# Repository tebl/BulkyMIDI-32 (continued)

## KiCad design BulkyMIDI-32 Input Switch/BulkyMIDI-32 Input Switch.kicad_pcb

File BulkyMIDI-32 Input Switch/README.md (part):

# BulkyMIDI-32 Input Switch
The complete *BulkyMIDI-32* consists of several separate PCB designs, many of them adding entirely separate functionality that can be used with or even without the main unit. This specific module, once fully assembled will allow you to switch between four different MIDI-inputs.

The selected input will be hooked up to the three thru-ports on the unit, allowing you to quickly switch between different keyboards, vintage computers and so on. Think of it as a simple 4-to-1 *MIDI Input Selector* chained to a 1-to-3 *MIDI Thru Box*. If you came here looking for something to switch between different audio sources, then have a look at [BulkyMIDI-32 Audio Switch](https://github.com/tebl/BulkyMIDI-32/tree/main/BulkyMIDI-32%20Audio%20Switch) instead.

For the design itself, I didn't want to use a microcontroller for such a trivial task, so it is implemented using logic chips instead. The end result is a set of flip-flops with a master reset, this latches the button pushed and you get an exciting little click from the corresponding relay. While this does mean that the device only switches electrical signals with the caveat that it doesn't have an understanding of MIDI-messages, and so it will cut regardless of what's passing through it. The upside is that since there is not processing, there is no *significant* delay added to it either.

- [1> Building the device](#1-building-the-device)
  - [1.1> Soldering it together](#11-soldering-it-together)
  - [1.2> Without front panel](#12-without-front-panel)
  - [1.3> Including front panel](#13-including-front-panel)
  - [1.4> Finishing touches](#14-finishing-touches)
- [2> Schematic](#2-schematic)
- [3> BOM](#3-bom)

# 1> Building the device
Building a device such as this assumes you have at least minor experience soldering things together, recommended is that you at the very least have access to a soldering station with adjustable temperature. If currently available, you should probably start with 60/40 rosin core solder as the lead-free alternatives tends to be a bit harder to work with.

With requirements for basic equipment sorted, we need to talk a bit about what you want to achieve while building this project. The reason I ask is that while you can build a functional *BulkyMIDI-32 Input Switch* by using this module by itself, there is certainly a case for having the option of building a complete version of it - this would normally include a front panel, a faceplates for the top of the unit as well as a cosmetic one to go on the front. 

Now that you know what you want to build, we can get started on the most expensive step in any build process - shopping! So, head on over to the [BOM](#3-bom)-section for some information on what kind of components that you'll need. While I would have liked to give you specific part numbers for "reputable" electronic part suppliers, I can't afford to shop there so I usually make due with what I can find on sites such as ebay, AliExpress and any similar sites that sell cheap chinese components. The downside to this is that I can't link to a part directly and expect it to stay listed, so you'll need to consider the description listed as *suggested search terms* instead of looking at them as part numbers. I can't provide you with anything else because I can't afford to do so.

## 1.1> Soldering it together
The construction of this unit should be fairly straight-forward, just take your time in order to make sure everything goes into place - more or less straight. I usually recommend starting by having a good look at the PCBs, try to figure out where all of the listed components go and in which orientation they go in (most of the information should be clearly marked on the silkscreen).

I will usually try to install components sorted by their physical size, doing it this way means you'll have an easier time keeping everything from looking somewhat crooked. This is your board, your build and you want it perfect - don't you? If you said no, then go sit in the corner because I worked hard on creating this for myself and whoever wants to build one.

Here we've already gotten started by installing all of the resistors needed, making sure that we use the correct values for each position on the board. While doing this, it is always a good recommendation to try and keep the colour bands in the same orientation - mostly because it makes it easier to spot mistakes later on. In various positions on the board you'll find five 470 &#8486;, these are the load resistors for the LEDs (includes the one on the front panel). This value may be suitable for use with cheap coloured LEDs, but for those that are *clear*, *blue* or in any way marked as *bright* - then you need to use a significantly higher value here. When in doubt, either test with a CR2032-battery - or - just install 2k2 &#8486; or even 3k3 &#8486; depending on your preference.

There are quite a few 1n4148 diodes in several locations on the board, these are polarized and for that reason we need to pay particular attention that the black band on the component matches up with those of marked on the PCB.

Sockets should be installed for the singe IC needed for the complete unit. With that in place I've also installed the monolithic disc capacitors, these are all unpolarized and for the ones without any specific markings we will install 100nF capacitors (the code *104* will be printed on the component). Note that a single capacitor marked *C10*, directly to the right of *U1*, has a different value from the others, it is 22nF and will have the code *223* printed on the component. This is also the only that has a value printed on the PCB.

The next component we're going to install are the *2n3904* NPN-transistors, these have a flat side and a round side that needs to be matched to the shape printed on the silkscreen. Putting them in the wrong way around will usually create tiny smoke-bombs instead of performing their intended purpose. While there are components available that have pre-bent legs matching those on the footprint, I've not seen them at a reasonable price - so I just bend the legs outward myself and firmly push down on them until they sit slightly above the board. Doing it this way will usually end up with some twisting slightly, but that is the cost of doing it the cheap way.

Next up are the polarized capacitors, these need to go in the right way for them to function as expected. The stripe on the side of the capacitor denotes the negative side of it, this should be matched up with the filled in area of the footprint. When in doubt, just put the longer pin into the other hole (marked with a "+"). For the most part we won't be anywhere near any relevant voltage rating, but the higher rated ones will generally be physically larger - the one at *C2* should be rated at 16v or 25v, mainly as we physically won't have room for much else.

Here we've added a common DC barrel connector (5.5mm x 2.1mm) to the board, followed by the four HK-19F-DC 5V relays. The relays have a tendency to come with crooked pins and we may need to do a bit of careful bending in order to get them into the board, there is also a little indent on one end that need to matched up with that on the board (similar to those of ICs).

> NB! If at some point you're wondering why there are only two yellow relays in this previous image as well as some of those shown later, this is simply because I ran out and had to wait for more to arrive in the mail.

Depending on your life decisions up to this point, the assembly from this point continues in one or the other direction:
- [1.2> Without front panel](#12-without-front-panel)
- [1.3> Including front panel](#13-including-front-panel)

## 1.2> Without front panel

So you resisted the temptation to build the complete version, choosing instead to cut corners wherever possible? Well, that's OK too. I'm not judging. Call it a general observation.

There's not much that we need to do, mainly just install the single 3mm power LED (the longer LED goes into the round pad). The four switches are standard right-angle switches, the recommended way to install them is simply to solder a single pin then reheat and adjust its alignment before soldering in the rest of the pins.

If you have a faceplate, the board that goes on top of the unit, add some 20mm hex standoffs to each of the four corners before continuing on to the next part of the build.

- [1.4> Finishing touches](#14-finishing-touches)

## 1.3> Including front panel

The [Input Switch Panel](https://github.com/tebl/BulkyMIDI-32/tree/main/BulkyMIDI-32%20Input%20Switch%20Panel) have its own set of documentation going into the various steps required to put it together correctly, a finished unit looking like what is shown above. In particular we need to ensure that the hex standoffs have been aligned so that a *flat* side is lined up with the left and right edges of the board, the nuts on the back needs to have a similar flat side matched to the top and bottom. You may need to trim these slightly with a sharp knife or a file. 

Starting with installing 20mm standoffs, making sure that these have a *flat* side pointing towards the inside of the PCB. With the alignment correct you should be able to line up the pin headers, insert the panel into the board without having to use more than a minimum amount of force. Your selected top faceplate is installed on the top of it all, here I'm just using a second set of standoff instead of screws since we'll be removing them again later.

At this point we've not actually soldered them together yet, mostly to ensure that everything comes together correctly before we actually do so. Push the panel firmly so that it sits towards the back of the cutouts, then solder the pins into place - afterwards we just trim the excess parts of the pin headers.

When soldered, everything should stay where it should be and before continuing on we just remove the faceplate again before moving onto the next step.

- [1.4> Finishing touches](#14-finishing-touches)

## 1.4> Finishing touches

If you've made it this far, you're almost ready to simply start using it. What's missing in order to test it is the three ICs that needs to be inserted into their sockets, so just get that out of the way before you forget to do so. Each IC needs to be installed in their specified orientation, that usually means matching up the indent on the socket to the indent or dot on your chips.

The device is powered using a 5v DC barrel jack (center positive) similar to just about everything else found in this repository, just make sure that what you're using is from a somewhat respected brand. Personally I'm using a *MEAN WELL GST25B05-P1J* that has served me well for these projects, but this specific model has a Europlug on it so you may need to look for something more relevant to your needs. While you may be tempted to plug MIDI-devices into it at this point, at least connect it to power by itself - and see if something explodes first. When clicking a button on the front you should be able to hear a small click from the corresponding relay.

The only step that's remaining is to just screw the faceplates back on the top of the device with proper screws, once that's in place we can also add the front faceplate as well. All that remains now is trying it out with equipment that you would consider easily replacable, such as other *BulkyMIDI-32* designs.

# 2> Schematic
The supplied KiCad files should be sufficient as both a schematic and as a  starting point for ordering PCBs (basically you could just zip the contents of the export folder and upload that on a fabrication site), the schematic is also available in [PDF-format](https://github.com/tebl/BulkyMIDI-32/tree/main/documentation/schematic) and this is what you'll need to print and work your way through this things don't work as expected after assembly.

# 3> BOM
Most parts should be easy to get a hold of from your favourite local electronic component shop, but given that I don't have access to such shops where I live so everything was based on whatever I could get cheapest from eBay/AliExpress (free shipping, but plan on waiting 3-4 weeks for delivery). Components in parenthesis can be considered optional for features beyond the more basic functionality, but where's the fun in that? You deserve the complete package.

| Reference                  | Item                                                              | Count | Order  |
| -------------------------- | ----------------------------------------------------------------- | ----- | ------ |
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
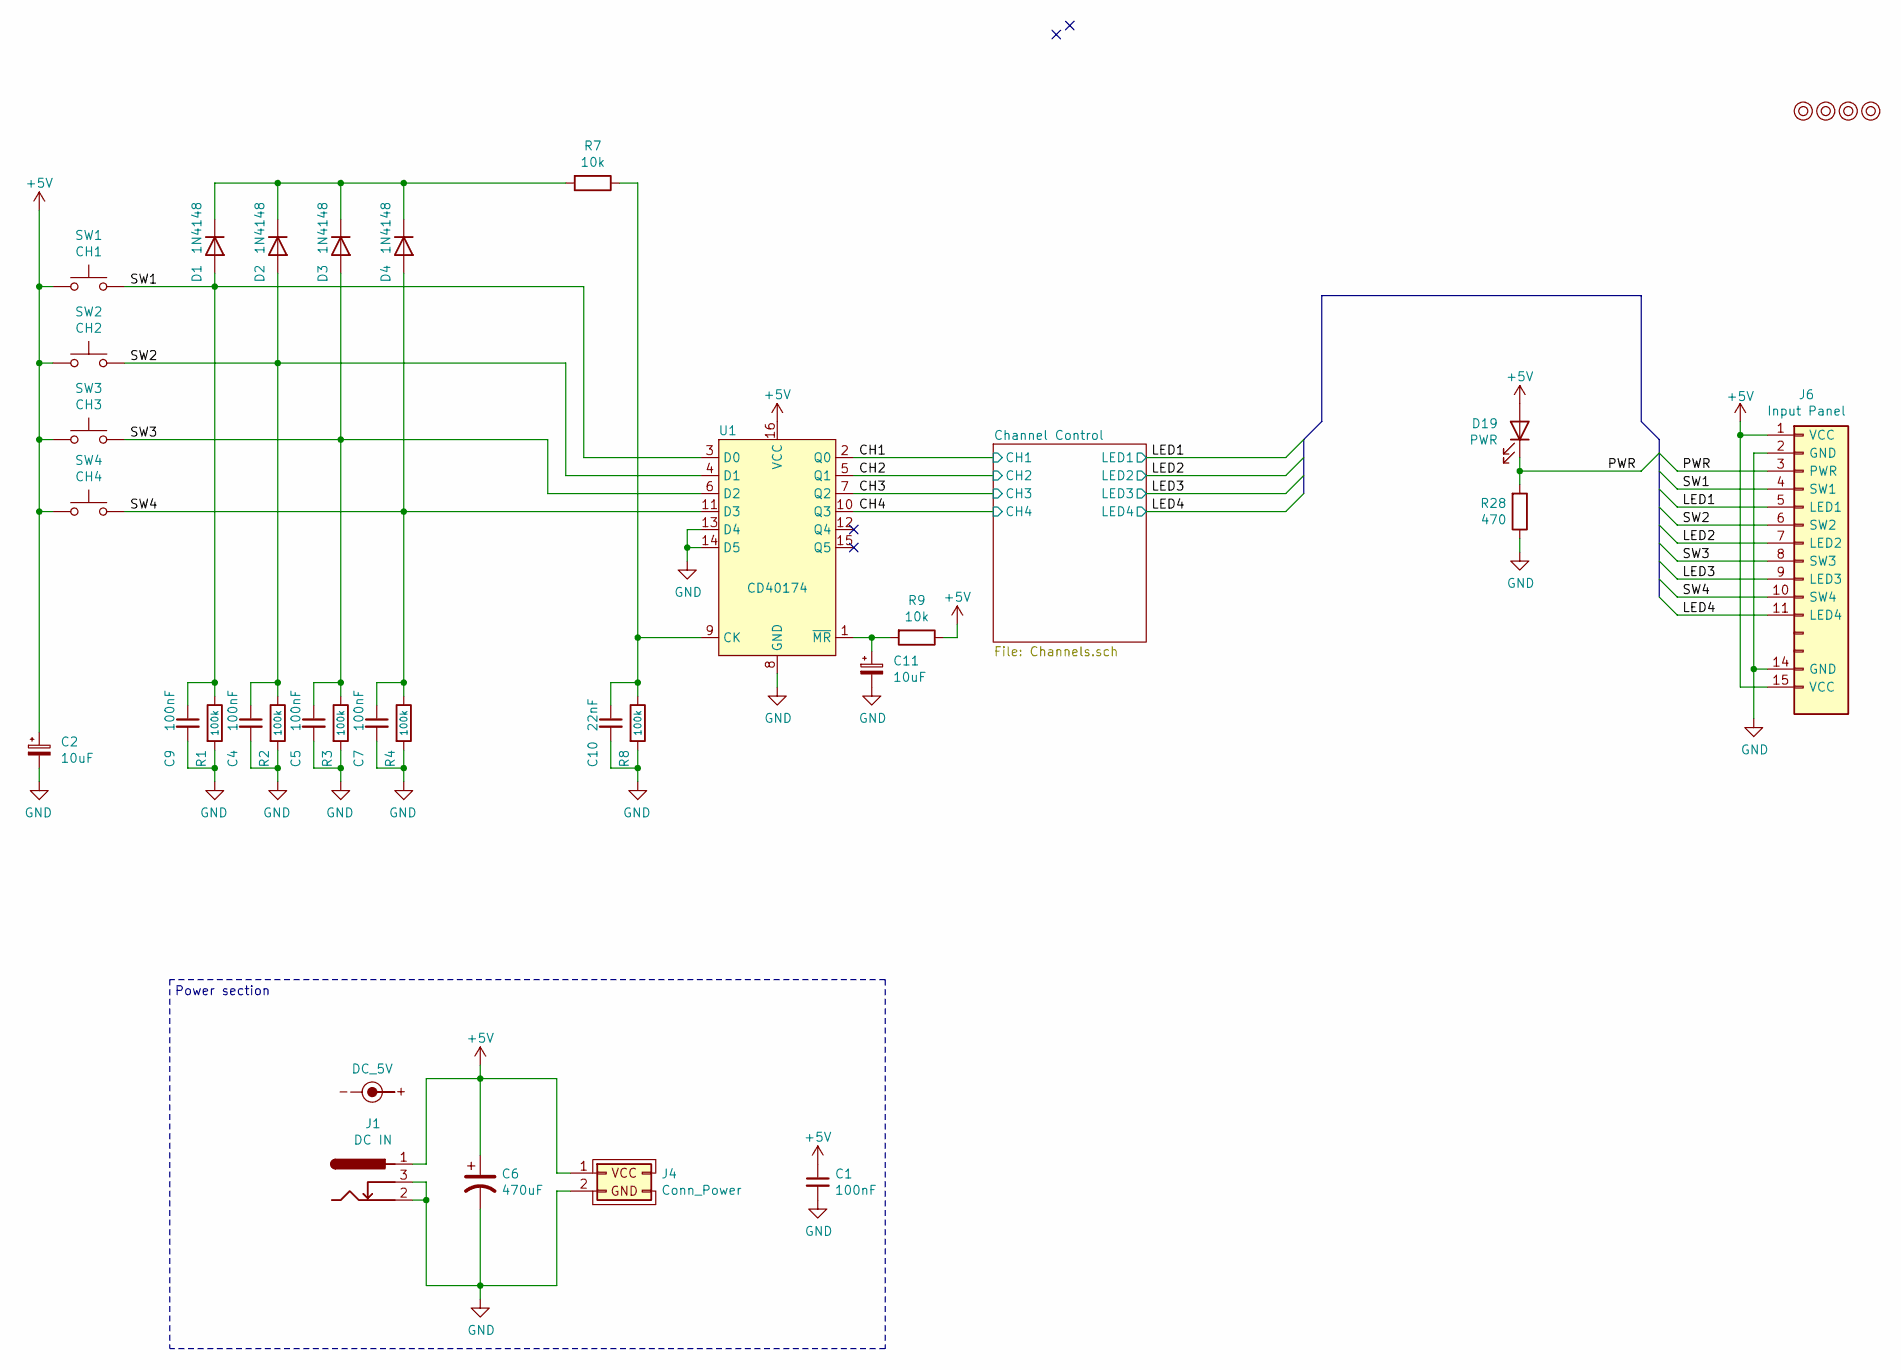
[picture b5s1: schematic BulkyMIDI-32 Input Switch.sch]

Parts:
C1, C4, C5, C7, C9: 100nF; C_Disc_D4.7mm_W2.5mm_P5.00mm
C2, C11: 10uF; CP_Radial_D4.0mm_P2.00mm
C6: 470uF; CP_Radial_D8.0mm_P3.50mm
C10: 22nF; C_Disc_D4.7mm_W2.5mm_P5.00mm
D1, D2, D3, D4: 1N4148; D_DO-35_SOD27_P7.62mm_Horizontal
D19: PWR; LED_D3.0mm
J1: DC IN; BARREL_JACK
J4: Conn_Power
J6: Input Panel; Input_Panel
M1, M2, M3, M4: Mounting; M3
R1, R2, R3, R4, R8: 100k; R_Axial_DIN0207_L6.3mm_D2.5mm_P10.16mm_Horizontal
R7, R9: 10k; R_Axial_DIN0207_L6.3mm_D2.5mm_P10.16mm_Horizontal
R28: 470; R_Axial_DIN0207_L6.3mm_D2.5mm_P10.16mm_Horizontal
SW1: CH1; SW_Tactile_SPST_Angled_PTS645Vx39-2LFS
SW2: CH2; SW_Tactile_SPST_Angled_PTS645Vx39-2LFS
SW3: CH3; SW_Tactile_SPST_Angled_PTS645Vx39-2LFS
SW4: CH4; SW_Tactile_SPST_Angled_PTS645Vx39-2LFS
SYM1: DC_5V; PWR_Specification
U1: CD40174; DIP-16_W7.62mm_Socket_LongPads

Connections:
+5V: C1.1, C2.1, C6.1, D19.2 (A), J1.1, J4.1 (VCC), J6.1 (VCC), J6.15 (VCC), R9.1, SW1.2, SW2.2, SW3.2, SW4.2, U1.16 (VCC); also elsewhere on the board
/CH1: U1.2 (Q0); also elsewhere on the board
/CH2: U1.5 (Q1); also elsewhere on the board
/CH3: U1.7 (Q2); also elsewhere on the board
/CH4: U1.10 (Q3); also elsewhere on the board
/LED1: J6.5 (LED1); also elsewhere on the board
/LED2: J6.7 (LED2); also elsewhere on the board
/LED3: J6.9 (LED3); also elsewhere on the board
/LED4: J6.11 (LED4); also elsewhere on the board
/PWR: D19.1 (K), J6.3 (PWR), R28.2
/SW1: C9.1, D1.2 (A), J6.4 (SW1), R1.1, SW1.1, U1.3 (D0)
/SW2: C4.1, D2.2 (A), J6.6 (SW2), R2.1, SW2.1, U1.4 (D1)
/SW3: C5.1, D3.2 (A), J6.8 (SW3), R3.1, SW3.1, U1.6 (D2)
/SW4: C7.1, D4.2 (A), J6.10 (SW4), R4.1, SW4.1, U1.11 (D3)
GND: C1.2, C2.2, C4.2, C5.2, C6.2, C7.2, C9.2, C10.2, C11.2, J1.2, J1.3, J4.2 (GND), J6.2 (GND), J6.14 (GND), R1.2, R2.2, R3.2, R4.2, R8.2, R28.1, U1.8 (GND), U1.13 (D4), U1.14 (D5); also elsewhere on the board
unnamed: C10.1, R7.1, R8.1, U1.9 (CK)
unnamed: C11.1, R9.2, U1.1 (~MR)
unnamed: D1.1 (K), D2.1 (K), D3.1 (K), D4.1 (K), R7.2

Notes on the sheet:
Power section

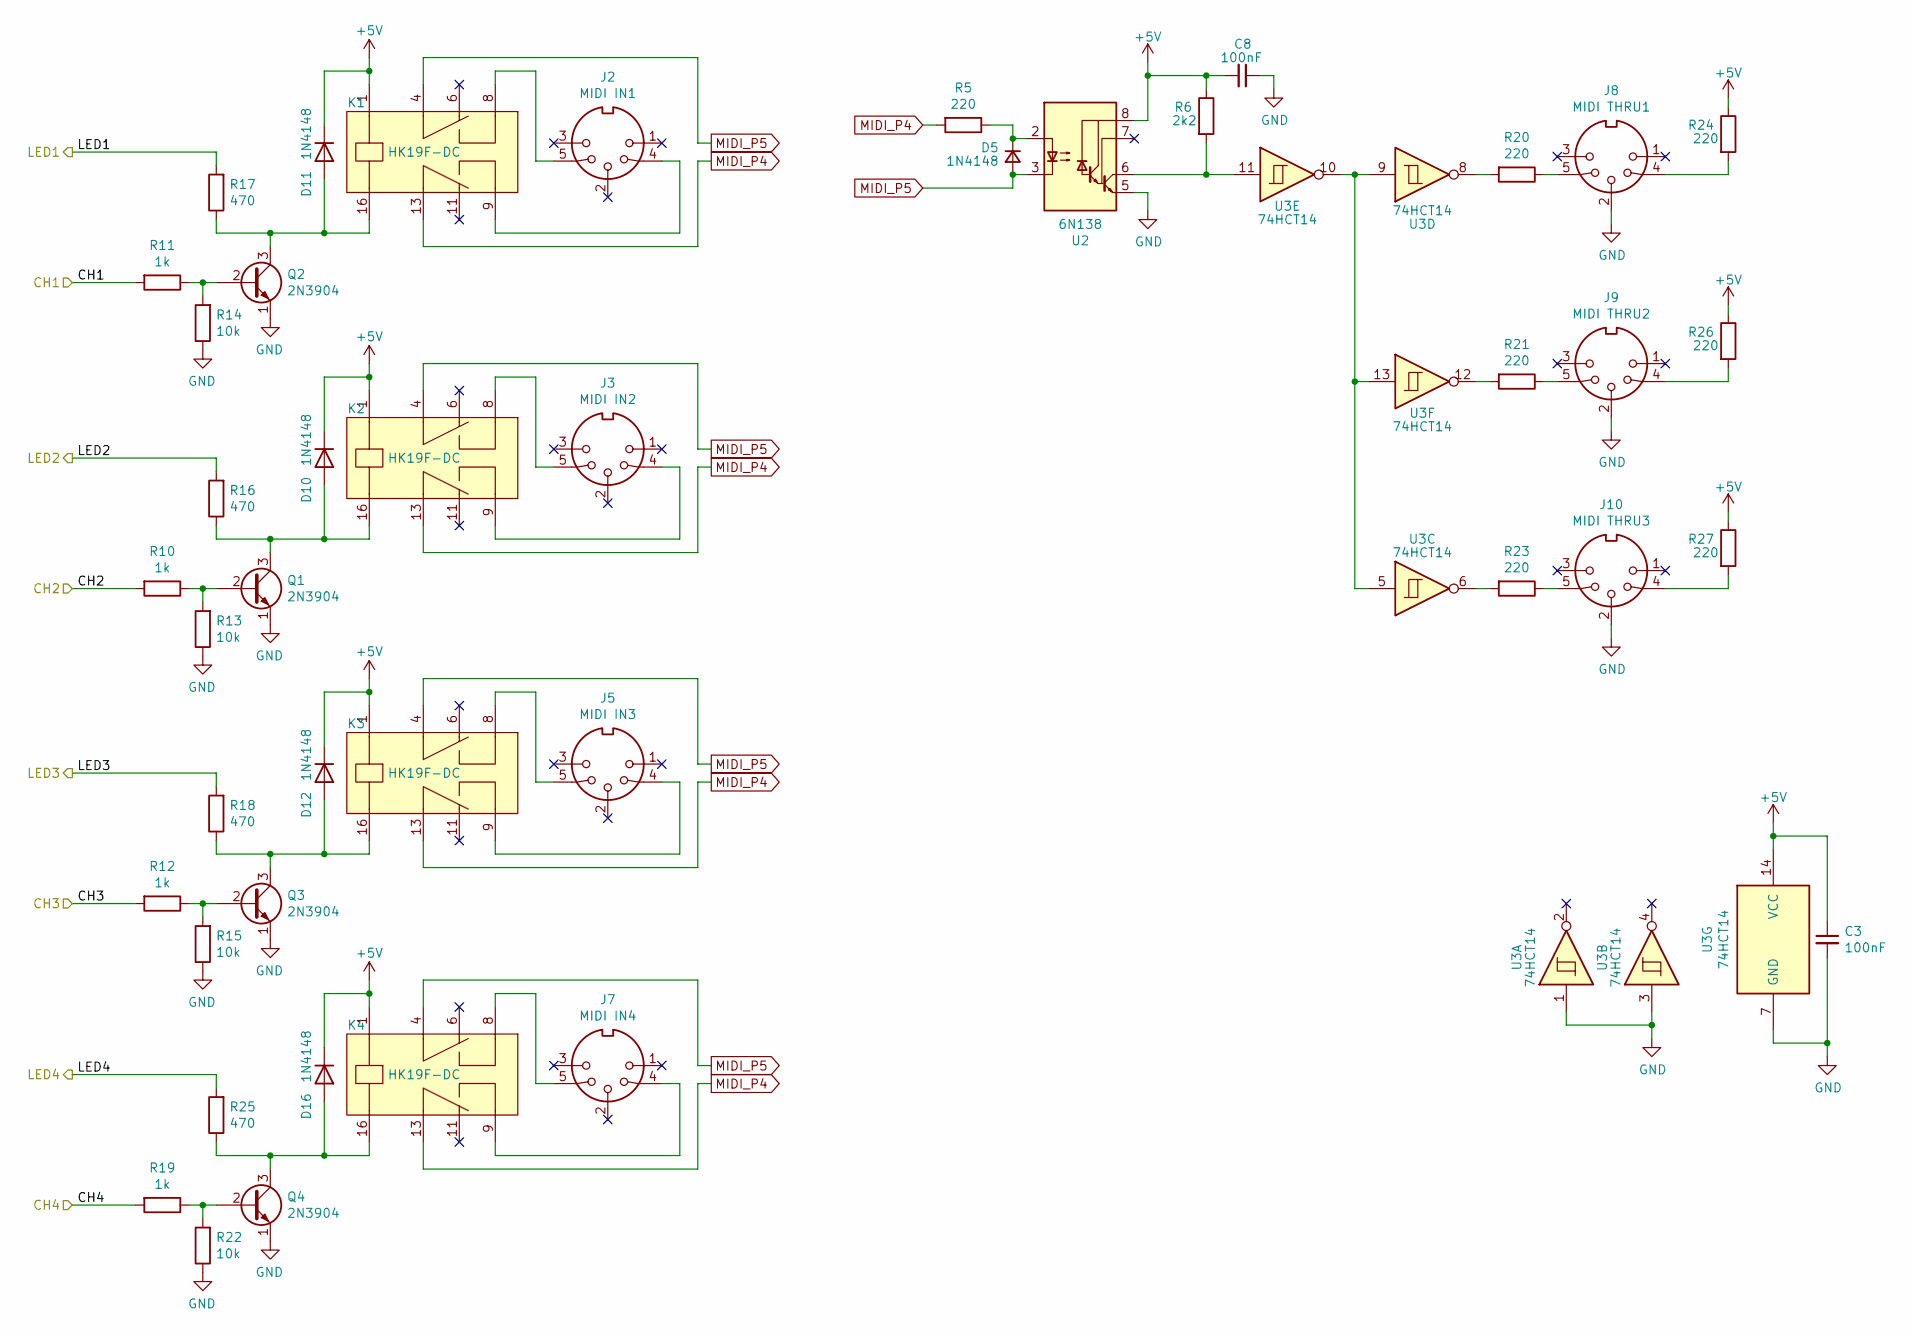
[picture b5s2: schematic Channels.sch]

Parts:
C3, C8: 100nF; C_Disc_D4.7mm_W2.5mm_P5.00mm
D5, D10, D11, D12, D16: 1N4148; D_DO-35_SOD27_P7.62mm_Horizontal
J2: MIDI IN1; DIN5_MIDI
J3: MIDI IN2; DIN5_MIDI
J5: MIDI IN3; DIN5_MIDI
J7: MIDI IN4; DIN5_MIDI
J8: MIDI THRU1; DIN5_MIDI
J9: MIDI THRU2; DIN5_MIDI
J10: MIDI THRU3; DIN5_MIDI
K1, K2, K3, K4: HK19F-DC
Q1, Q2, Q3, Q4: 2N3904; TO-92_Inline_Wide
R5, R20, R21, R23, R24, R26, R27: 220; R_Axial_DIN0207_L6.3mm_D2.5mm_P10.16mm_Horizontal
R6: 2k2; R_Axial_DIN0207_L6.3mm_D2.5mm_P10.16mm_Horizontal
R10, R11, R12, R19: 1k; R_Axial_DIN0207_L6.3mm_D2.5mm_P10.16mm_Horizontal
R13, R14, R15, R22: 10k; R_Axial_DIN0207_L6.3mm_D2.5mm_P10.16mm_Horizontal
R16, R17, R18, R25: 470; R_Axial_DIN0207_L6.3mm_D2.5mm_P10.16mm_Horizontal
U2: 6N138; DIP-8_W7.62mm_Socket_LongPads
U3: 74HCT14; DIP-14_W7.62mm_Socket_LongPads

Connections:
+5V: C3.1, C8.2, D10.1 (K), D11.1 (K), D12.1 (K), D16.1 (K), K1.1, K2.1, K3.1, K4.1, R6.1, R24.1, R26.1, R27.1, U2.8 (VCC), U3.14 (VCC); also elsewhere on the board
/CH1: R11.2; also elsewhere on the board
/CH2: R10.2; also elsewhere on the board
/CH3: R12.2; also elsewhere on the board
/CH4: R19.2; also elsewhere on the board
/LED1: R17.2; also elsewhere on the board
/LED2: R16.2; also elsewhere on the board
/LED3: R18.2; also elsewhere on the board
/LED4: R25.2; also elsewhere on the board
GND: C3.2, C8.1, J8.2, J9.2, J10.2, Q1.1 (E), Q2.1 (E), Q3.1 (E), Q4.1 (E), R13.1, R14.1, R15.1, R22.1, U2.5 (GND), U3.1, U3.3, U3.7 (GND); also elsewhere on the board
MIDI_P4: K1.13 (COM_2), K2.13 (COM_2), K3.13 (COM_2), K4.13 (COM_2), R5.2
MIDI_P5: D5.2 (A), K1.4 (COM_1), K2.4 (COM_1), K3.4 (COM_1), K4.4 (COM_1), U2.3 (C2)
unnamed: D5.1 (K), R5.1, U2.2 (C1)
unnamed: D10.2 (A), K2.16, Q1.3 (C), R16.1
unnamed: D11.2 (A), K1.16, Q2.3 (C), R17.1
unnamed: D12.2 (A), K3.16, Q3.3 (C), R18.1
unnamed: D16.2 (A), K4.16, Q4.3 (C), R25.1
unnamed: J2.4, K1.9 (NO_2)
unnamed: J2.5, K1.8 (NO_1)
unnamed: J3.4, K2.9 (NO_2)
unnamed: J3.5, K2.8 (NO_1)
unnamed: J5.4, K3.9 (NO_2)
unnamed: J5.5, K3.8 (NO_1)
unnamed: J7.4, K4.9 (NO_2)
unnamed: J7.5, K4.8 (NO_1)
unnamed: J8.4, R24.2
unnamed: J8.5, R20.1
unnamed: J9.4, R26.2
unnamed: J9.5, R21.1
unnamed: J10.4, R27.2
unnamed: J10.5, R23.1
unnamed: Q1.2 (B), R10.1, R13.2
unnamed: Q2.2 (B), R11.1, R14.2
unnamed: Q3.2 (B), R12.1, R15.2
unnamed: Q4.2 (B), R19.1, R22.2
unnamed: R6.2, U2.6 (VO2), U3.11
unnamed: R20.2, U3.8
unnamed: R21.2, U3.12
unnamed: R23.2, U3.6
unnamed 47: U2.7 (VO1); also elsewhere on the board
unnamed: U3.5, U3.9, U3.10, U3.13

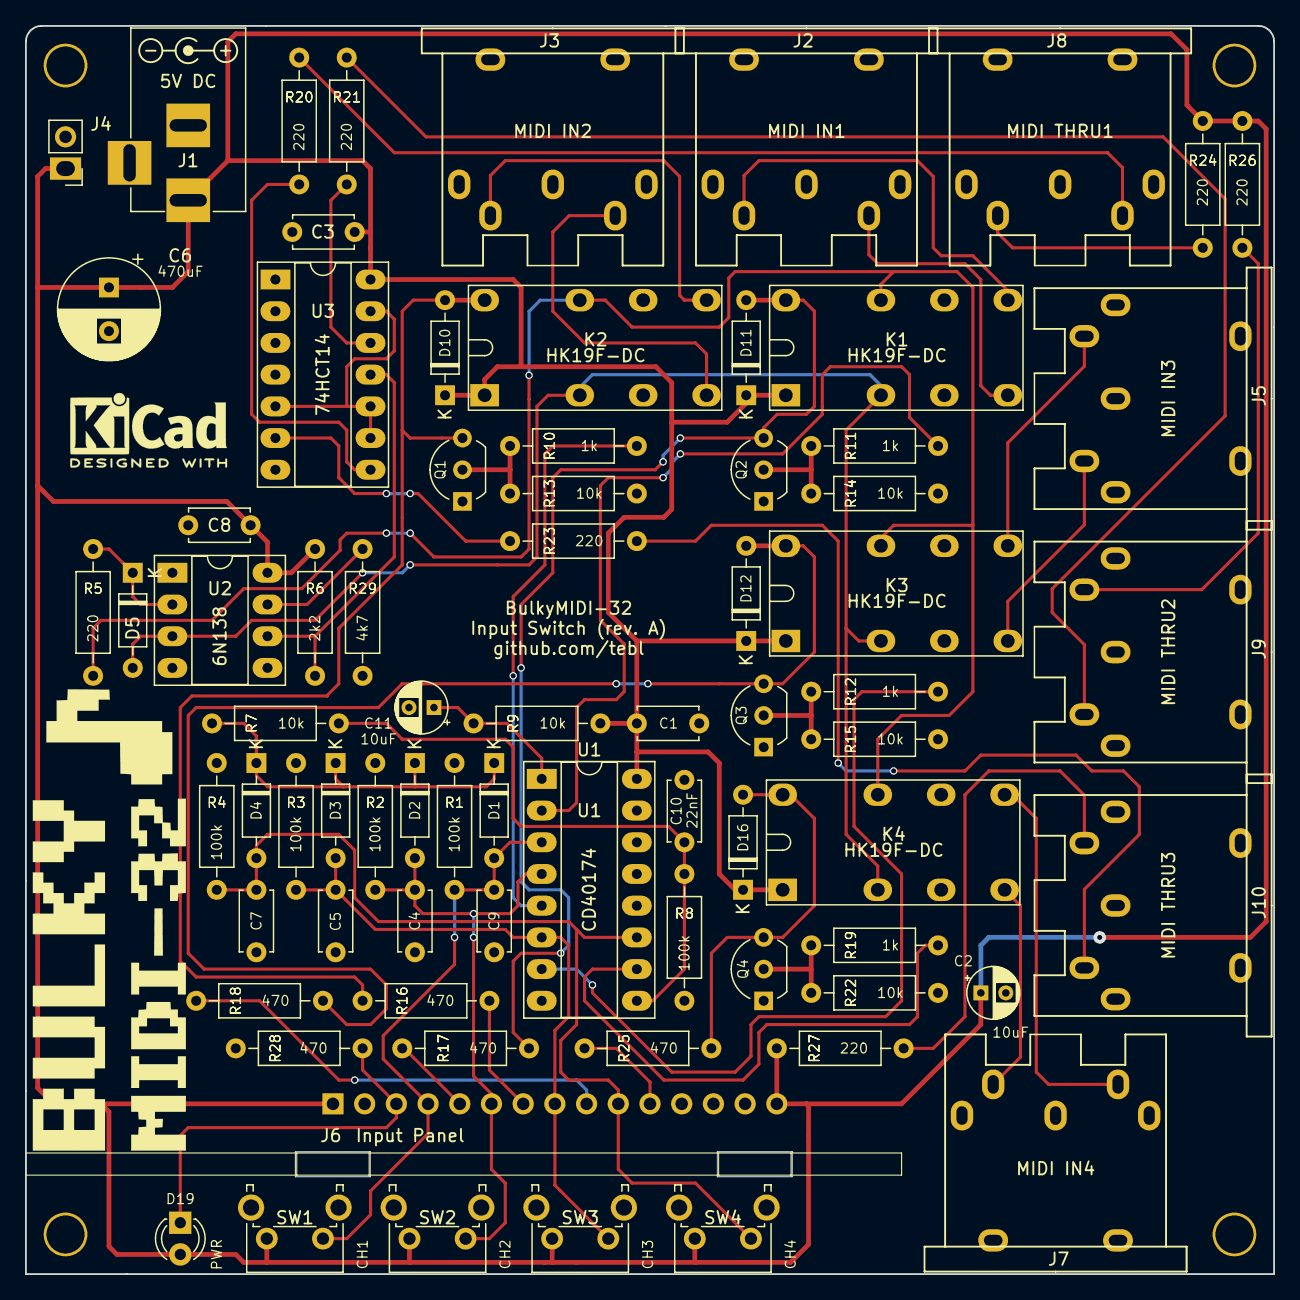
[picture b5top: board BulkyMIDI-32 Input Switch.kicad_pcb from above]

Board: 2 copper layers, 100.0 x 100.0 mm, 80 parts (0 on the bottom side), 49 nets.

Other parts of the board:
R29: 4k7; R_Axial_DIN0207_L6.3mm_D2.5mm_P10.16mm_Horizontal

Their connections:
GND: R29.2; also elsewhere on the board
unnamed 47: R29.1; also elsewhere on the board

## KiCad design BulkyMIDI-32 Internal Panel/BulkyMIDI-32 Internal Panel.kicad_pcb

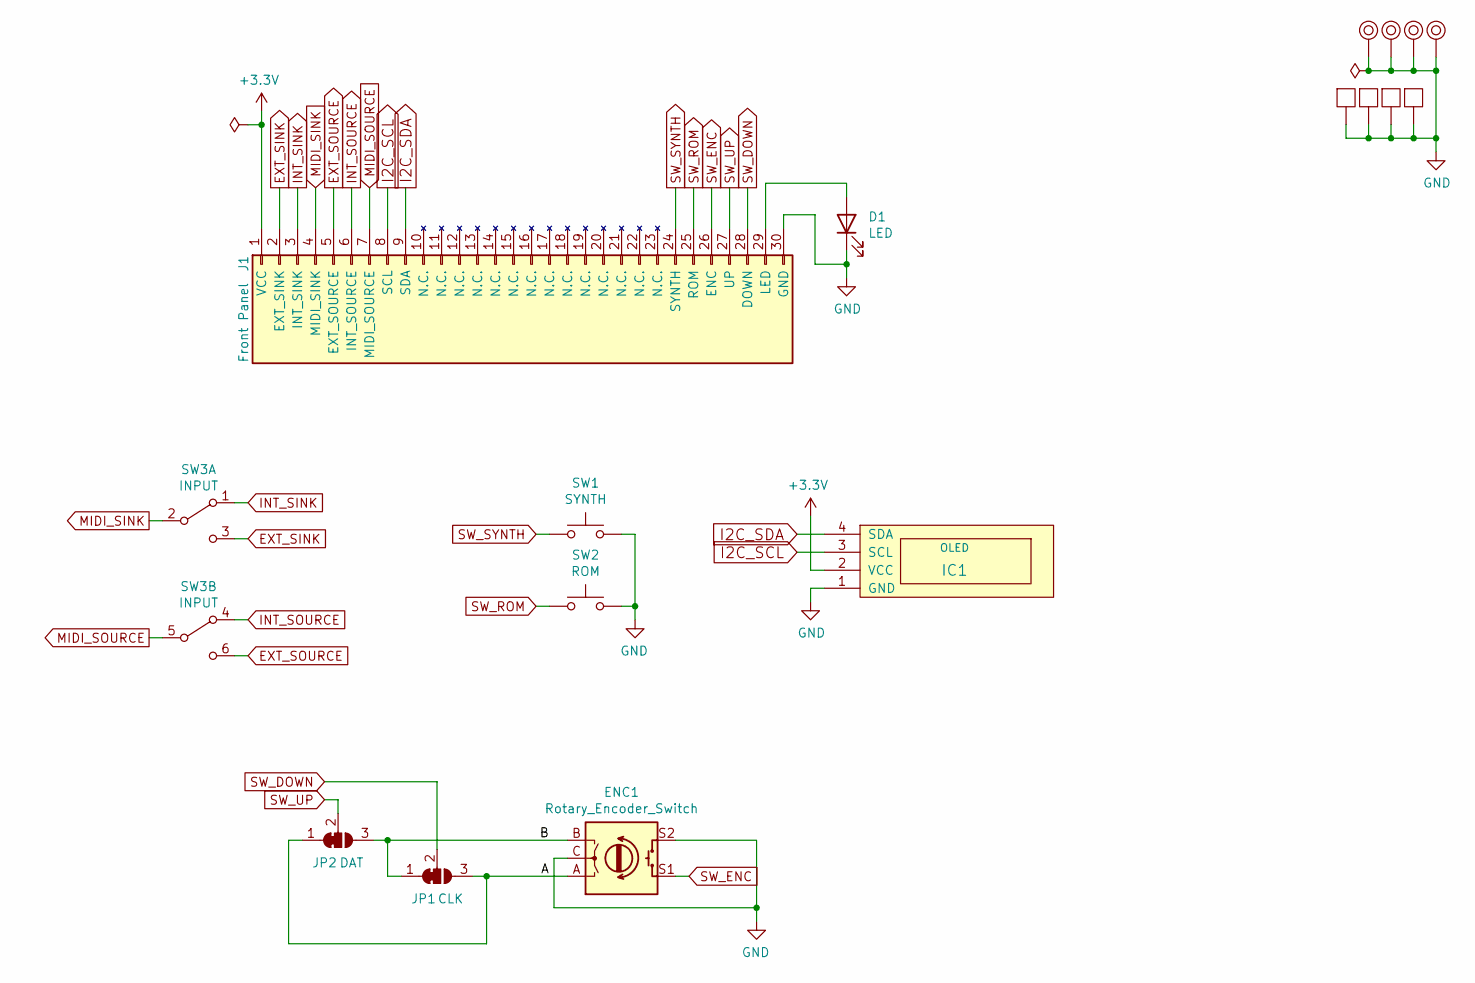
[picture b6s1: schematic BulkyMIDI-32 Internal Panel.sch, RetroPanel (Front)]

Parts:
D1: LED; LED_D5.0mm
ENC1: Rotary_Encoder_Switch; RotaryEncoder_Alps_EC11E-Switch_Vertical_H20mm
IC1: OLED; 0.91_I2C_OLED
J1: Front Panel; Internal_Panel_Angle
JP1: CLK; SolderJumper-3_P1.3mm_Open_Pad1.0x1.5mm
JP2: DAT; SolderJumper-3_P1.3mm_Open_Pad1.0x1.5mm
M1, M2, M3, M4: Mounting_Pin; M3_pin
M5, M7, M9, M10: Mounting_Pad; Pad_pin
SW1: SYNTH; SW_PUSH_6mm
SW2: ROM; SW_PUSH_6mm
SW3: INPUT; dpdt_switch_black

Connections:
+3V3: IC1.2 (VCC), J1.1 (VCC)
/A: ENC1.A, JP1.3 (B), JP2.1 (A)
/B: ENC1.B, JP1.1 (A), JP2.3 (B)
EXT_SINK: J1.2 (EXT_SINK), SW3.3 (C)
EXT_SOURCE: J1.5 (EXT_SOURCE), SW3.6 (C)
GND: D1.1 (K), ENC1.C, ENC1.S2, IC1.1 (GND), J1.30 (GND), M1.1, M2.1, M3.1, M4.1, M5.1, M7.1, M9.1, M10.1, SW1.2, SW2.2
I2C_SCL: IC1.3 (SCL), J1.8 (SCL)
I2C_SDA: IC1.4 (SDA), J1.9 (SDA)
INT_SINK: J1.3 (INT_SINK), SW3.1 (A)
INT_SOURCE: J1.6 (INT_SOURCE), SW3.4 (A)
MIDI_SINK: J1.4 (MIDI_SINK), SW3.2 (B)
MIDI_SOURCE: J1.7 (MIDI_SOURCE), SW3.5 (B)
unnamed: D1.2 (A), J1.29 (LED)
SW_DOWN: J1.28 (DOWN), JP1.2 (C)
SW_ENC: ENC1.S1, J1.26 (ENC)
SW_ROM: J1.25 (ROM), SW2.1
SW_SYNTH: J1.24 (SYNTH), SW1.1
SW_UP: J1.27 (UP), JP2.2 (C)

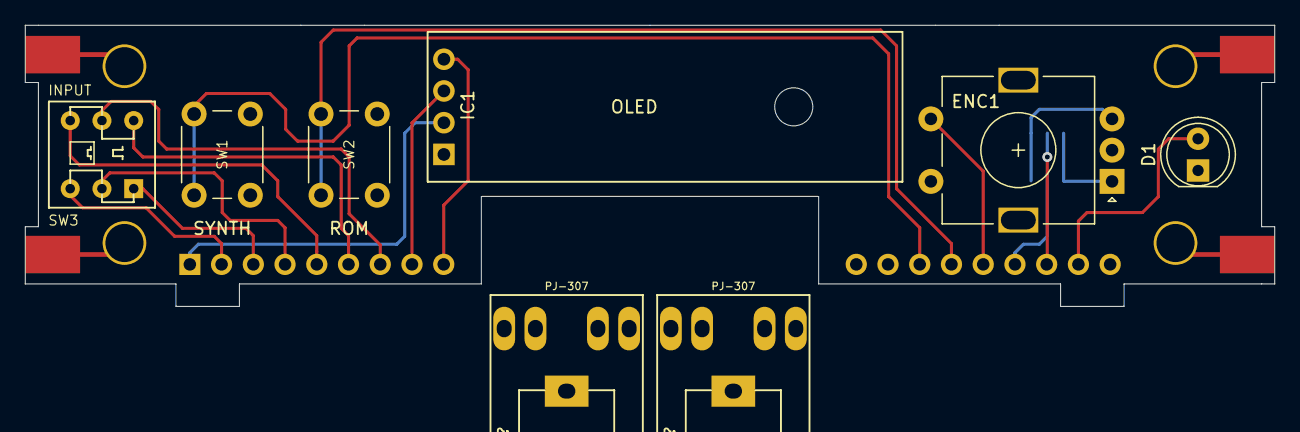
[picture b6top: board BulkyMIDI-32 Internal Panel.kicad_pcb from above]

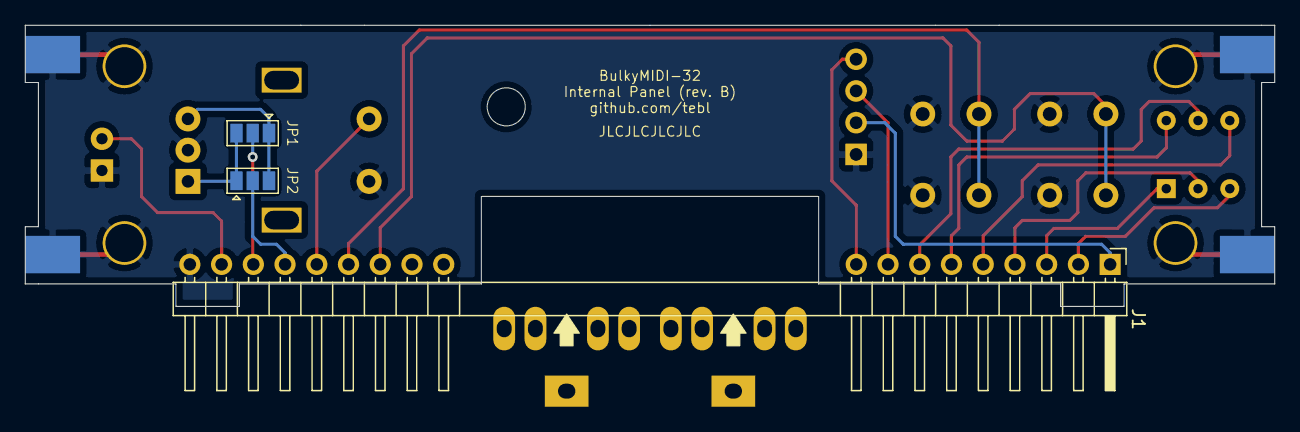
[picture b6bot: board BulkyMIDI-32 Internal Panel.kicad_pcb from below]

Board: 2 copper layers, 100.0 x 22.5 mm, 19 parts (3 on the bottom side), 18 nets.

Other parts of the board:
J?: PJ-307
J?#2: PJ-307

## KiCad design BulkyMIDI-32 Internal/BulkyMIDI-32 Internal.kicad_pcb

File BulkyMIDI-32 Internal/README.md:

https://minimidi.world/
https://polprog.net/blog/audigy2zs/

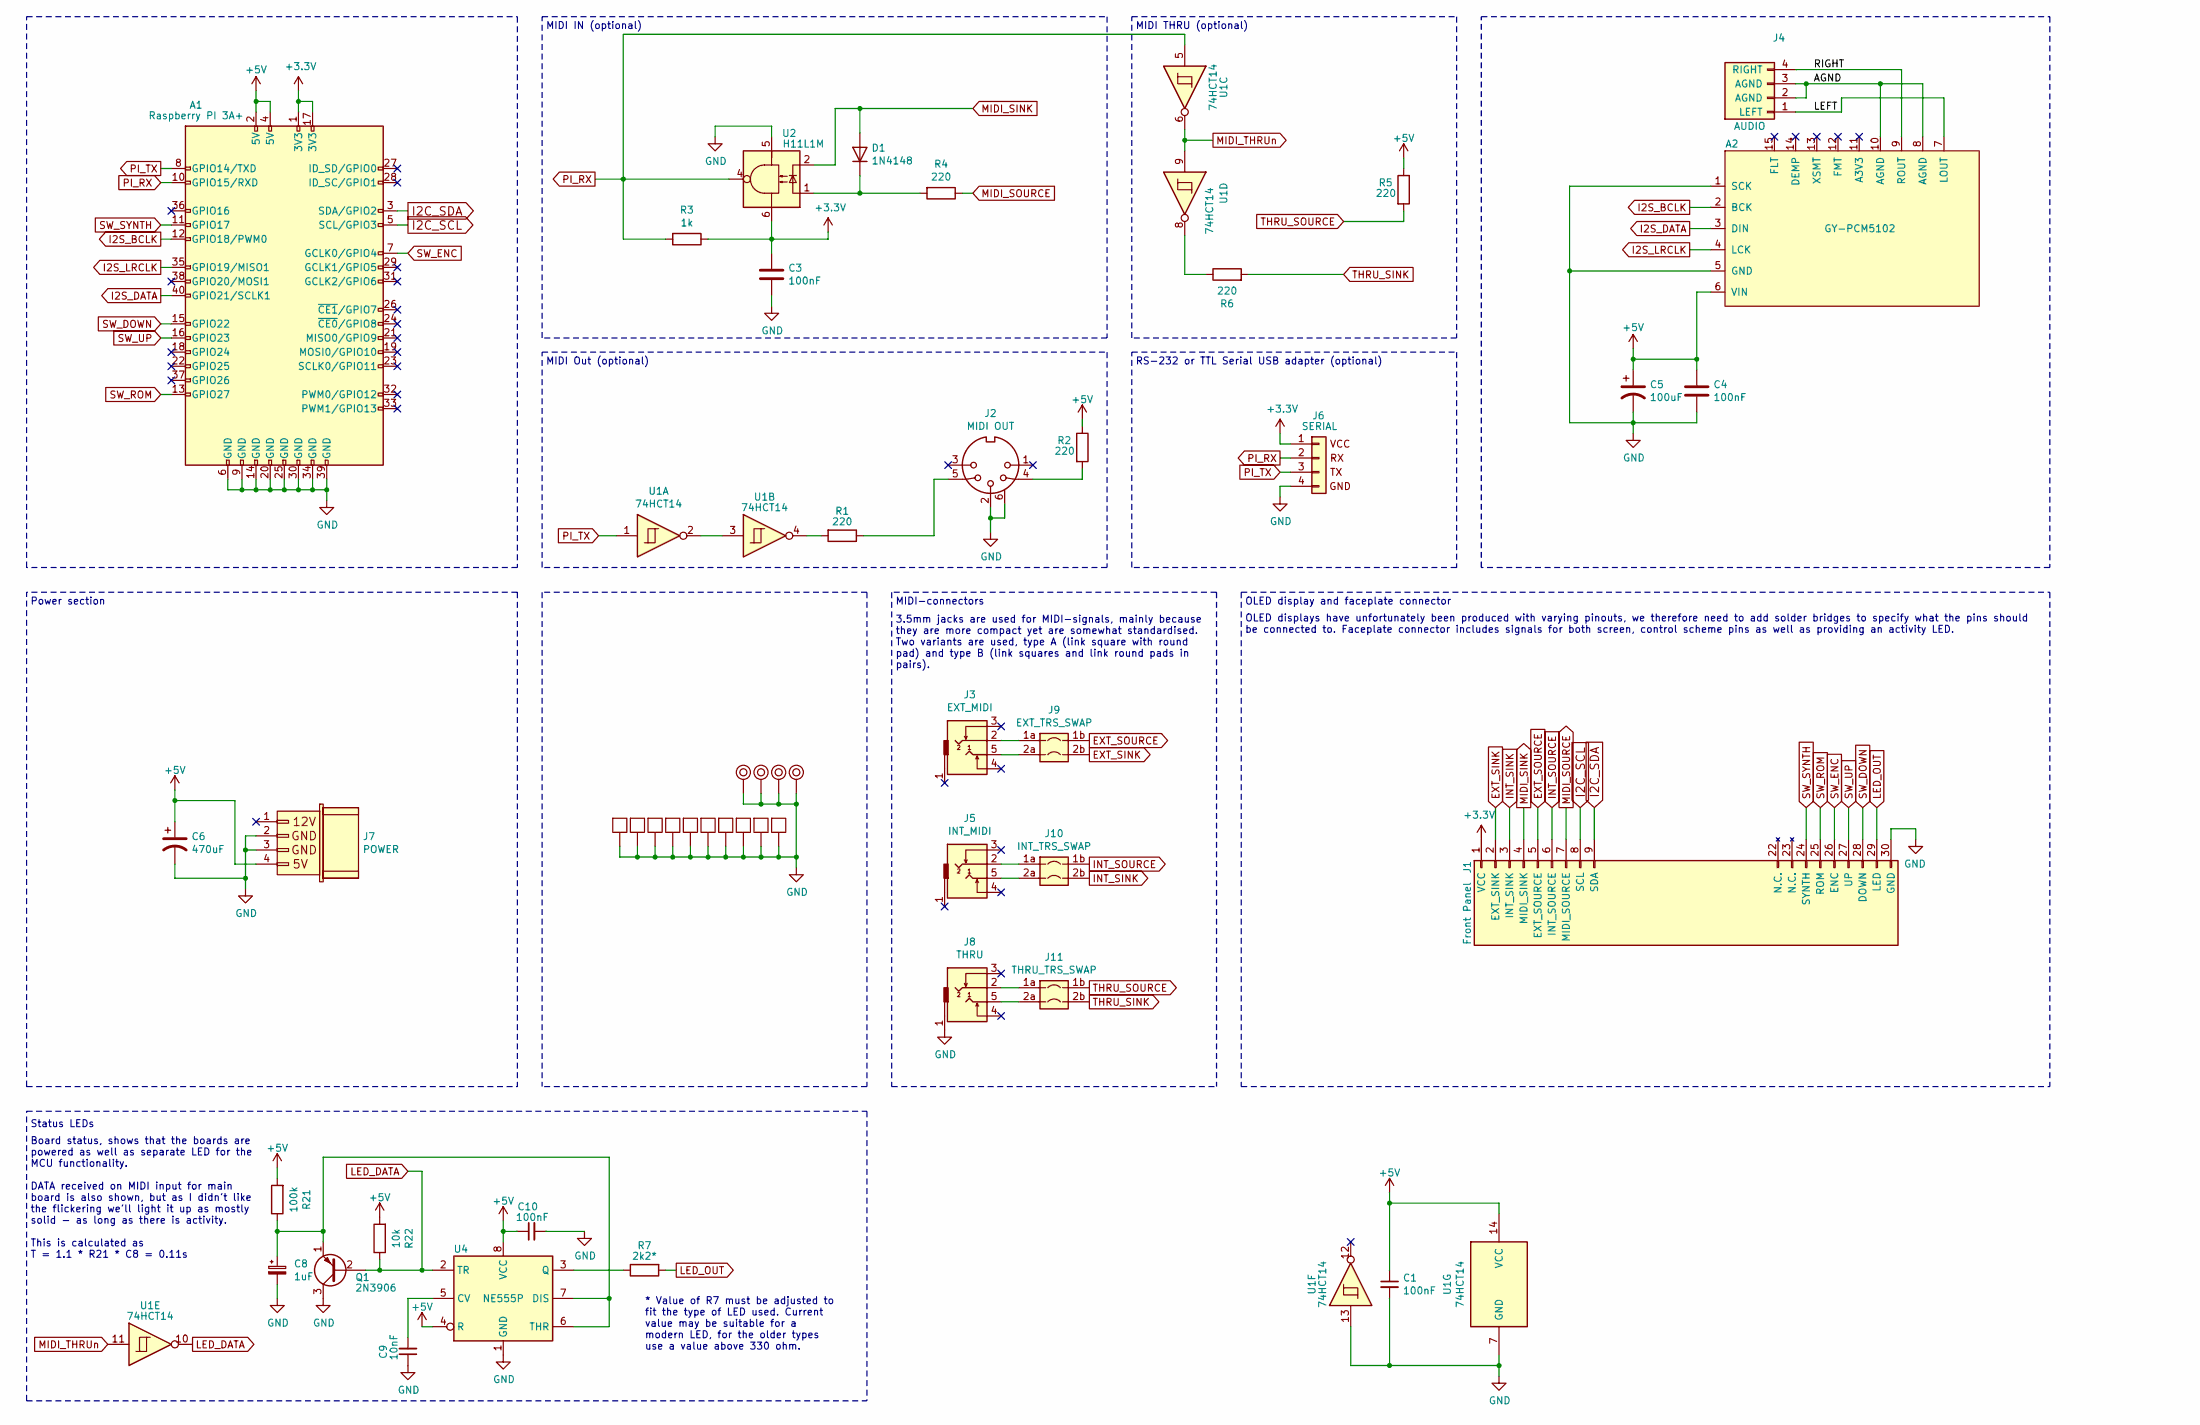
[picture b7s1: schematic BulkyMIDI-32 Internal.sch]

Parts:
A1: Raspberry PI 3A+; Raspberry_Pi_3A_Socketed_THT_FaceDown_MountingHoles
A2: GY-PCM5102
C1: 100nF; C_Disc_D5.0mm_W2.5mm_P5.00mm
C3, C4: 100nF; C_Rect_L7.0mm_W2.0mm_P5.00mm
C5: 100uF; CP_Radial_D6.3mm_P2.50mm
C6: 470uF; CP_Radial_D8.0mm_P3.50mm
C8: 1uF; CP_Radial_D5.0mm_P2.00mm
C9: 10nF; C_Disc_D4.7mm_W2.5mm_P5.00mm
C10: 100nF; C_Disc_D4.7mm_W2.5mm_P5.00mm
D1: 1N4148; D_DO-35_SOD27_P7.62mm_Horizontal
J1: Front Panel; Internal_Panel
J2: MIDI OUT; PinHeader_1x06_P2.54mm_Vertical
J3: EXT_MIDI; PJ-307_IN
J4: AUDIO; PinHeader_1x04_P2.54mm_Horizontal
J5: INT_MIDI; PJ-307_IN
J6: SERIAL; PinHeader_1x04_P2.54mm_Vertical
J7: POWER; Molex_KK-254_1x04_P2.54mm_Horizontal
J8: THRU; PJ-307_OUT
J9: EXT_TRS_SWAP; select_swappable
J10: INT_TRS_SWAP; select_swappable
J11: THRU_TRS_SWAP; select_swappable
M1, M2, M3, M16: Mounting_Pin; M3_pin
M5, M8, M9, M10, M11, M12, M13, M15: Mounting_Pad; Pad_pin
M7, M14: Mounting_Pad; B.Pad_pin
Q1: 2N3906; TO-92_Inline_Wide
R1, R2, R4, R5, R6: 220; R_Axial_DIN0207_L6.3mm_D2.5mm_P10.16mm_Horizontal
R3: 1k; R_Axial_DIN0207_L6.3mm_D2.5mm_P10.16mm_Horizontal
R7: 2k2*; R_Axial_DIN0207_L6.3mm_D2.5mm_P10.16mm_Horizontal
R21: 100k; R_Axial_DIN0207_L6.3mm_D2.5mm_P10.16mm_Horizontal
R22: 10k; R_Axial_DIN0207_L6.3mm_D2.5mm_P10.16mm_Horizontal
U1: 74HCT14; DIP-14_W7.62mm_Socket_LongPads
U2: H11L1M; DIP-6_W7.62mm_Socket_LongPads
U4: NE555P; DIP-8_W7.62mm_Socket_LongPads

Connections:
+3V3: A1.1 (3V3), A1.17 (3V3), C3.1, J1.1 (VCC), J6.1, R3.1, U2.6
+5V: A1.2 (5V), A1.4 (5V), A2.6 (VIN), C1.1, C4.1, C5.1, C6.1, C10.1, J7.4, R2.1, R5.1, R21.2, R22.2, U1.14 (VCC), U4.4 (R), U4.8 (VCC)
/AGND: A2.8 (AGND), A2.10 (AGND), J4.2 (AGND), J4.3 (AGND)
/LEFT: A2.7 (LOUT), J4.1 (LEFT)
/RIGHT: A2.9 (ROUT), J4.4 (RIGHT)
EXT_SINK: J1.2 (EXT_SINK), J9.2b
EXT_SOURCE: J1.5 (EXT_SOURCE), J9.1b
GND: A1.6 (GND), A1.9 (GND), A1.14 (GND), A1.20 (GND), A1.25 (GND), A1.30 (GND), A1.34 (GND), A1.39 (GND), A2.1 (SCK), A2.5 (GND), C1.2, C3.2, C4.2, C5.2, C6.2, C8.2, C9.1, C10.2, J1.30 (GND), J2.2, J2.6, J6.4, J7.2, J7.3, J8.1, M1.1, M2.1, M3.1, M5.1, M7.1, M8.1, M9.1, M10.1, M11.1, M12.1, M13.1, M14.1, M15.1, M16.1, Q1.3 (C), U1.7 (GND), U1.13, U2.5, U4.1 (GND)
I2C_SCL: A1.5 (SCL/GPIO3), J1.8 (SCL)
I2C_SDA: A1.3 (SDA/GPIO2), J1.9 (SDA)
I2S_BCLK: A1.12 (GPIO18/PWM0), A2.2 (BCK)
I2S_DATA: A1.40 (GPIO21/SCLK1), A2.3 (DIN)
I2S_LRCLK: A1.35 (GPIO19/MISO1), A2.4 (LCK)
INT_SINK: J1.3 (INT_SINK), J10.2b
INT_SOURCE: J1.6 (INT_SOURCE), J10.1b
LED_DATA: Q1.2 (B), R22.1, U1.10, U4.2 (TR)
LED_OUT: J1.29 (LED), R7.2
MIDI_SINK: D1.2 (A), J1.4 (MIDI_SINK), U2.2
MIDI_SOURCE: J1.7 (MIDI_SOURCE), R4.1
MIDI_THRUn: U1.6, U1.9, U1.11
unnamed: C8.1, Q1.1 (E), R21.1, U4.6 (THR), U4.7 (DIS)
unnamed: C9.2, U4.5 (CV)
unnamed: D1.1 (K), R4.2, U2.1
unnamed: J2.4, R2.2
unnamed: J2.5, R1.1
unnamed: J3.2, J9.1a
unnamed: J3.5, J9.2a
unnamed: J5.2, J10.1a
unnamed: J5.5, J10.2a
unnamed: J8.2, J11.1a
unnamed: J8.5, J11.2a
unnamed: R1.2, U1.4
unnamed: R6.1, U1.8
unnamed: R7.1, U4.3 (Q)
unnamed: U1.2, U1.3
PI_RX: A1.10 (GPIO15/RXD), J6.2, R3.2, U1.5, U2.4
PI_TX: A1.8 (GPIO14/TXD), J6.3, U1.1
SW_DOWN: A1.15 (GPIO22), J1.28 (DOWN)
SW_ENC: A1.7 (GCLK0/GPIO4), J1.26 (ENC)
SW_ROM: A1.13 (GPIO27), J1.25 (ROM)
SW_SYNTH: A1.11 (GPIO17), J1.24 (SYNTH)
SW_UP: A1.16 (GPIO23), J1.27 (UP)
THRU_SINK: J11.2b, R6.2
THRU_SOURCE: J11.1b, R5.2

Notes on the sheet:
Power section
OLED displays have unfortunately been produced with varying pinouts, we therefore need to add solder bridges to specify what the pins should be connected to. Faceplate connector includes signals for both screen, control scheme pins as well as providing an activity LED.
OLED display and faceplate connector
RS-232 or TTL Serial USB adapter (optional)
MIDI IN (optional)
MIDI THRU (optional)
MIDI Out (optional)
MIDI-connectors
3.5mm jacks are used for MIDI-signals, mainly because they are more compact yet are somewhat standardised. Two variants are used, type A (link square with round pad) and type B (link squares and link round pads in pairs).
Status LEDs
Board status, shows that the boards are powered as well as separate LED for the MCU functionality. DATA received on MIDI input for main board is also shown, but as I didn't like the flickering we'll light it up as mostly solid - as long as there is activity. This is calculated as T = 1.1 * R21 * C8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
* Value of R7 must be adjusted to fit the type of LED used. Current value may be suitable for a modern LED, for the older types use a value above 330 ohm.

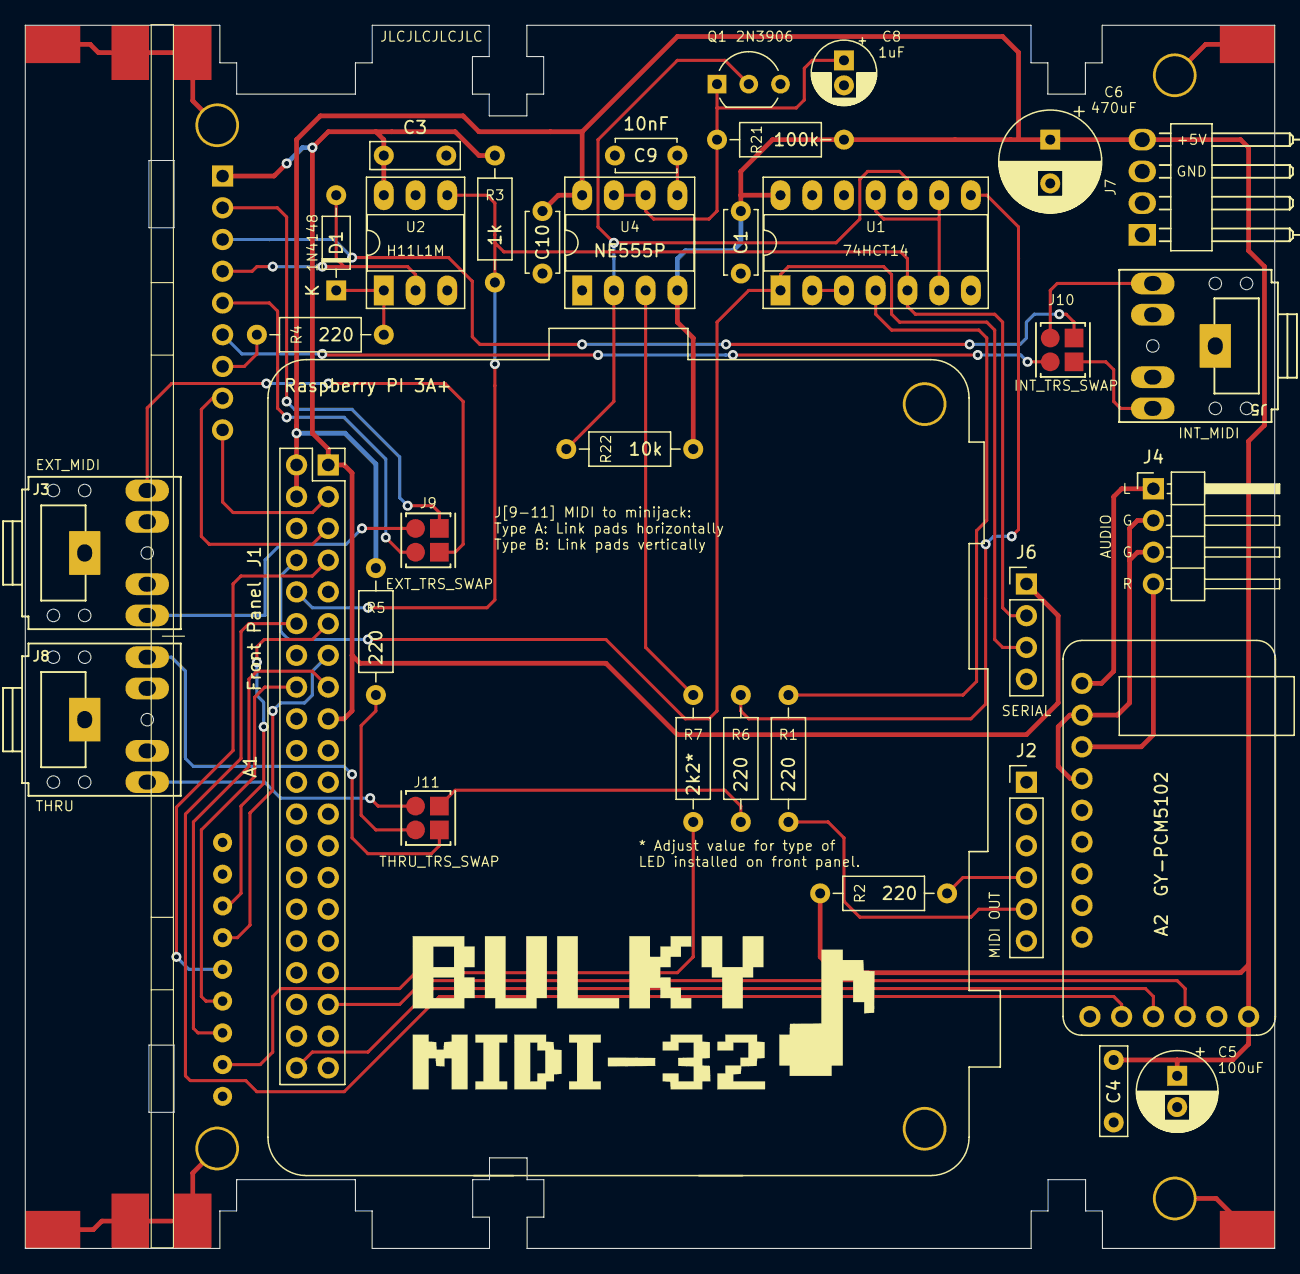
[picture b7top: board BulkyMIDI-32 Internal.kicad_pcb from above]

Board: 2 copper layers, 100.0 x 97.9 mm, 49 parts (0 on the bottom side), 44 nets.
